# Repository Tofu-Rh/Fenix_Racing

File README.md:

<!--  -->

# <div align="center"> Repositório Eletrônica </div>

##### Por Rhomulo Thiago (com "h" nos dois)

<p align="justify">Este repositório é destinado ao armazenamento, consulta e utilização de informações relacionadas a programação de sistemas embarcados na área da Eletrônica. Cada pasta é separada pelo nome de um software específico utilizado, contendo guias para novos membros e suas aplicações para a equipe. Abaixo tem-se o link para cada uma das pastas : </p>

- [Arduino IDE](https://github.com/Tofu-Rh/Fenix_Racing/tree/main/Arduino%20IDE)
- [STM32Cube](https://github.com/Tofu-Rh/Fenix_Racing/tree/main/STM32)
- [VScode](https://github.com/Tofu-Rh/Fenix_Racing/tree/main/VScode)

### Tenho interesse em aprender a modificar os arquivos do repositório, como posso fazer isso?
<p align="justify"> O GitHub é uma plataforma de hospedagem de código-fonte e colaboração para desenvolvedores. Ele fornece um ambiente centralizado para gerenciar projetos de software usando o sistema de controle de versão Git. Este site, que você está acessando, contém apenas o repositório nosso hospedado, porém é possível criar e modificar este repositório remotamente do seu computador. Todo este controle entre repositório remoto (Seu computador) com o do Github (Esta página) é feito através do Git Dash, um software indispensável, que ensinarei sua utilização passo a passo abaixo:  </p>

## 1. Instalação do Git 
Caso esteja utilizando o sistema operacional Windows, é necessário instalar o Git no seu PC pelo link a seguir: [Download do Git para Windows](https://git-scm.com/download/win).

Para usuários de macOS e Linux, o Git pode ser instalado diretamente através do gerenciador de pacotes. Para macOS, você pode usar o Homebrew com o comando `brew install git`. No Linux, geralmente o comando é `sudo apt-get install git` (para distribuições baseadas no Debian/Ubuntu) ou `sudo yum install git` (para distribuições baseadas no Red Hat/Fedora).

## 2. Configuração Inicial
Após a instalação do Git, configure seu nome de usuário e e-mail para os commits:
```bash
git config --global user.name "Seu Nome"
git config --global user.email "seuemail@example.com"
```
## 3. Clonando o Repositório
Para começar a trabalhar com o repositório, clone-o para o seu computador:
```bash
git clone https://github.com/Tofu-Rh/Fenix_Racing.git
```
## 4. Fazendo Alterações
Navegue até o diretório do repositório clonado:
```bash
cd Fenix_Racing
```
Crie uma nova branch para suas alterações:
```bash
git checkout -b nome-da-sua-branch
```
Faça suas alterações e adicione os arquivos modificados. Em seguida você podera dar commit das mudanças(pre-etapa para envia-las, comente bem oq você está alterando):
```bash
git add .
git commit -m "Descrição das alterações realizadas"
```

## 5. Enviando Alterações para o Repositório Remoto
Para enviar suas alterações para o GitHub, use o comando:
```bash
git push origin nome-da-sua-branch
```

## 6. Atualizando seu Repositório Local
Para atualizar seu repositório local com as últimas alterações do repositório remoto:
```bash
git pull origin main
```
## Ademais Comandos
Outros comandos para utilizar pelo git não são os mais utilizados, porém podem servir de valor:
 Para ver as alterações que foram feitas desde o último commit:
```bash
git diff
```
Para visualizar o histórico de commits do repositório:
```bash
git log (Para visualizar o histórico de commits do repositório:
```

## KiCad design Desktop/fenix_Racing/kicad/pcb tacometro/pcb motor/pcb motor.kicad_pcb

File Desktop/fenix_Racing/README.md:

<!--  -->

# <div align="center"> Repositório Eletrônica </div>

##### Por Rhomulo Thiago (com "h" nos dois)

Todos os projetos deste repositório estão organizados em branch's separadas pelo nome do software em específico utilizado pela área. Atente-se a nomeclatura seguida em cada um deles, para não virar bagunça. 

Se tá perdido e começou agora com o git de uma olhada nessa playlist :  https://youtube.com/playlist?list=PL9jCCY-sD3m-fLgYBpKHWVlHaEz9MDBnw

Lista de comandos do git : https://docs.google.com/document/d/13YfJPmGhQXhTQrYP2JQ6DnHkJQH8FnN9acvRIVPWNEk/edit?usp=sharing

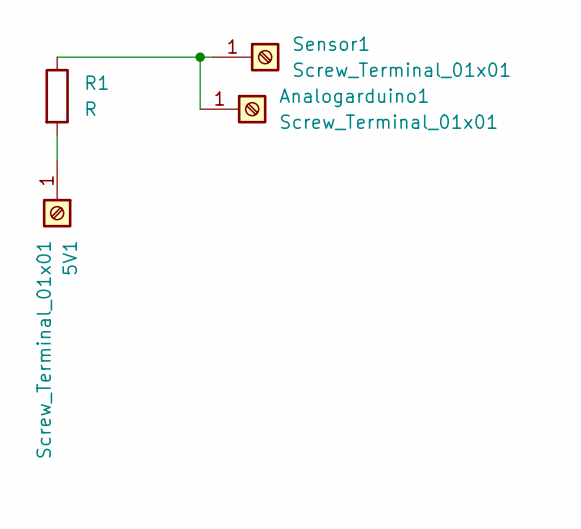
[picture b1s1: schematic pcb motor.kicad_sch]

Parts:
5V1: Screw_Terminal_01x01; TerminalBlock_MetzConnect_360271_1x01_Horizontal_ScrewM3.0_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
Analogarduino1: Screw_Terminal_01x01; TerminalBlock_MetzConnect_360271_1x01_Horizontal_ScrewM3.0_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
R1: R; R_Axial_DIN0411_L9.9mm_D3.6mm_P12.70mm_Horizontal
Sensor1: Screw_Terminal_01x01; TerminalBlock_MetzConnect_360271_1x01_Horizontal_ScrewM3.0_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

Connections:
unnamed: 5V1.1, R1.2
unnamed: Analogarduino1.1, R1.1, Sensor1.1

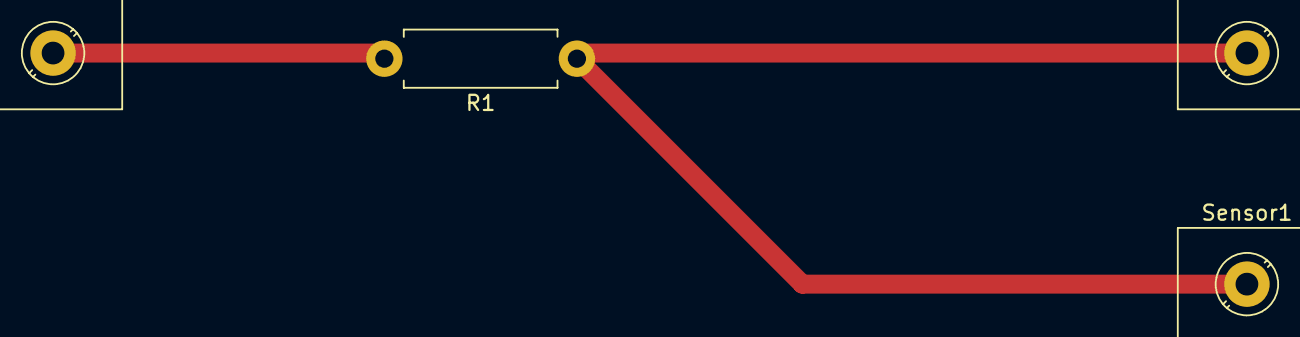
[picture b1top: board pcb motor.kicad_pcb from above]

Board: 2 copper layers, 4 parts (0 on the bottom side), 2 nets.

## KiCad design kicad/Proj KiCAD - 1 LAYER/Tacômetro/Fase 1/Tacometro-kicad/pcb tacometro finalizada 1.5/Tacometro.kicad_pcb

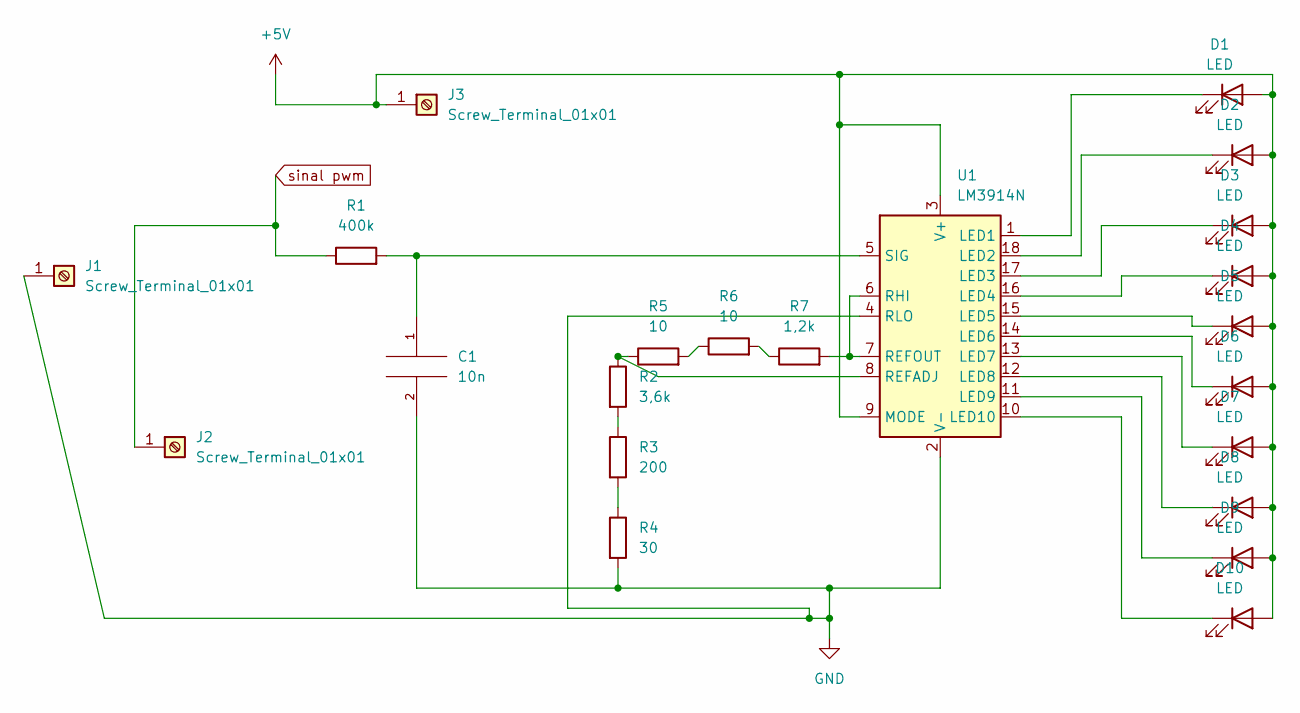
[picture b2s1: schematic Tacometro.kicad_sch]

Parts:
C1: 10n; C_Disc_D16.0mm_W5.0mm_P10.00mm
D1, D2, D3, D4, D5, D6, D7, D8, D9, D10: LED; LED_D5.0mm
J1, J2, J3: Screw_Terminal_01x01; PinHeader_1x01_P1.00mm_Vertical
R1: 400k; R_Axial_DIN0207_L6.3mm_D2.5mm_P10.16mm_Horizontal
R2: 3,6k; R_Axial_DIN0207_L6.3mm_D2.5mm_P10.16mm_Horizontal
R3: 200; R_Axial_DIN0207_L6.3mm_D2.5mm_P10.16mm_Horizontal
R4: 30; R_Axial_DIN0207_L6.3mm_D2.5mm_P10.16mm_Horizontal
R5, R6: 10; R_Axial_DIN0207_L6.3mm_D2.5mm_P10.16mm_Horizontal
R7: 1,2k; R_Axial_DIN0207_L6.3mm_D2.5mm_P10.16mm_Horizontal
U1: LM3914N; DIP-18_W7.62mm

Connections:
+5V: D1.2 (A), D2.2 (A), D3.2 (A), D4.2 (A), D5.2 (A), D6.2 (A), D7.2 (A), D8.2 (A), D9.2 (A), D10.2 (A), J3.1, U1.3 (V+), U1.9 (MODE)
GND: C1.2, J1.1, R4.2, U1.2 (V-), U1.4 (RLO)
unnamed: C1.1, R1.2, U1.5 (SIG)
unnamed: D1.1 (K), U1.1 (LED1)
unnamed: D2.1 (K), U1.18 (LED2)
unnamed: D3.1 (K), U1.17 (LED3)
unnamed: D4.1 (K), U1.16 (LED4)
unnamed: D5.1 (K), U1.15 (LED5)
unnamed: D6.1 (K), U1.14 (LED6)
unnamed: D7.1 (K), U1.13 (LED7)
unnamed: D8.1 (K), U1.12 (LED8)
unnamed: D9.1 (K), U1.11 (LED9)
unnamed: D10.1 (K), U1.10 (LED10)
unnamed: R2.1, R5.1, U1.8 (REFADJ)
unnamed: R2.2, R3.1
unnamed: R3.2, R4.1
unnamed: R5.2, R6.1
unnamed: R6.2, R7.1
unnamed: R7.2, U1.6 (RHI), U1.7 (REFOUT)
sinal pwm: J2.1, R1.1

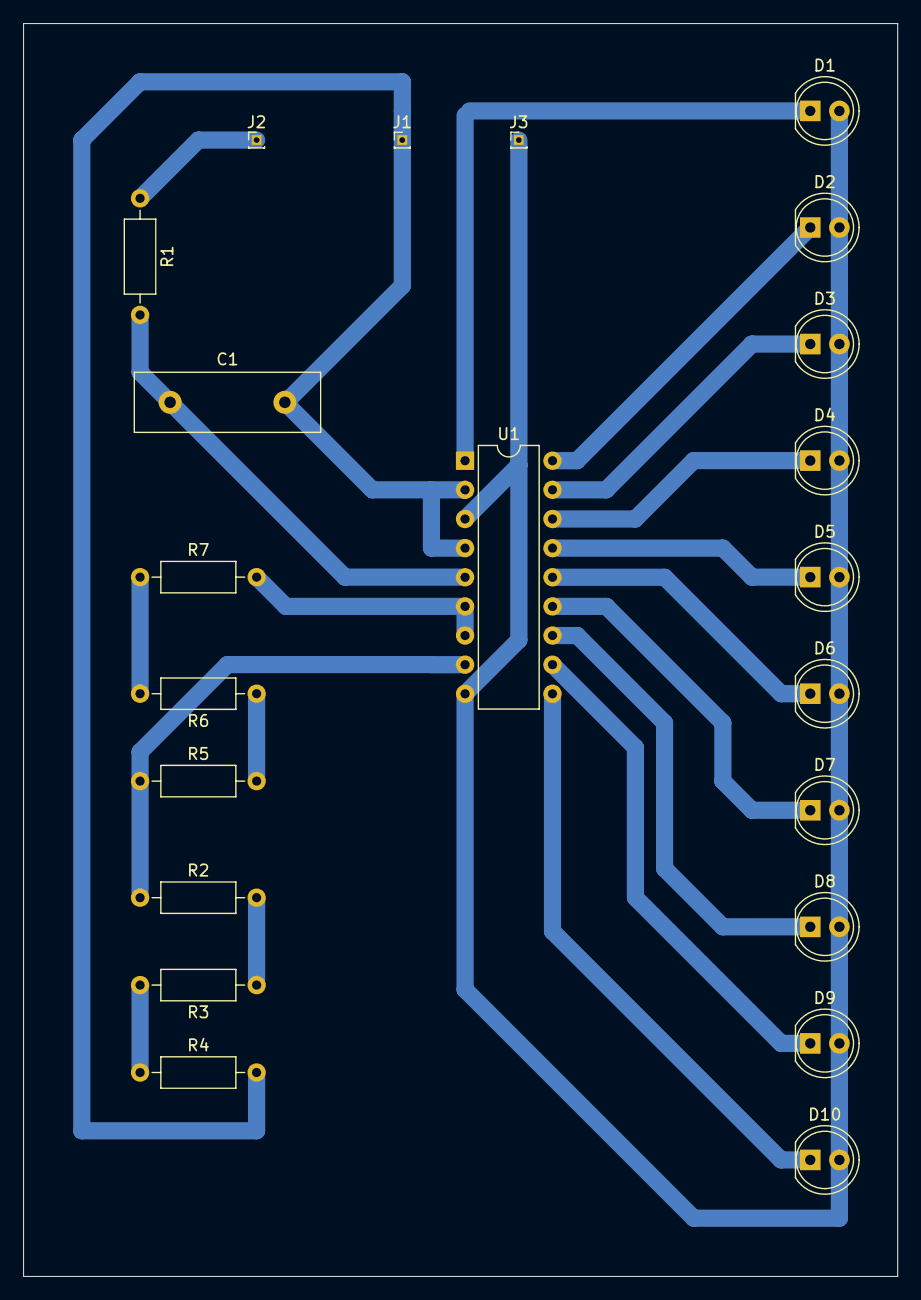
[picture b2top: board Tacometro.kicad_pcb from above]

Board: 2 copper layers, 76.2 x 109.2 mm, 22 parts (0 on the bottom side), 20 nets.

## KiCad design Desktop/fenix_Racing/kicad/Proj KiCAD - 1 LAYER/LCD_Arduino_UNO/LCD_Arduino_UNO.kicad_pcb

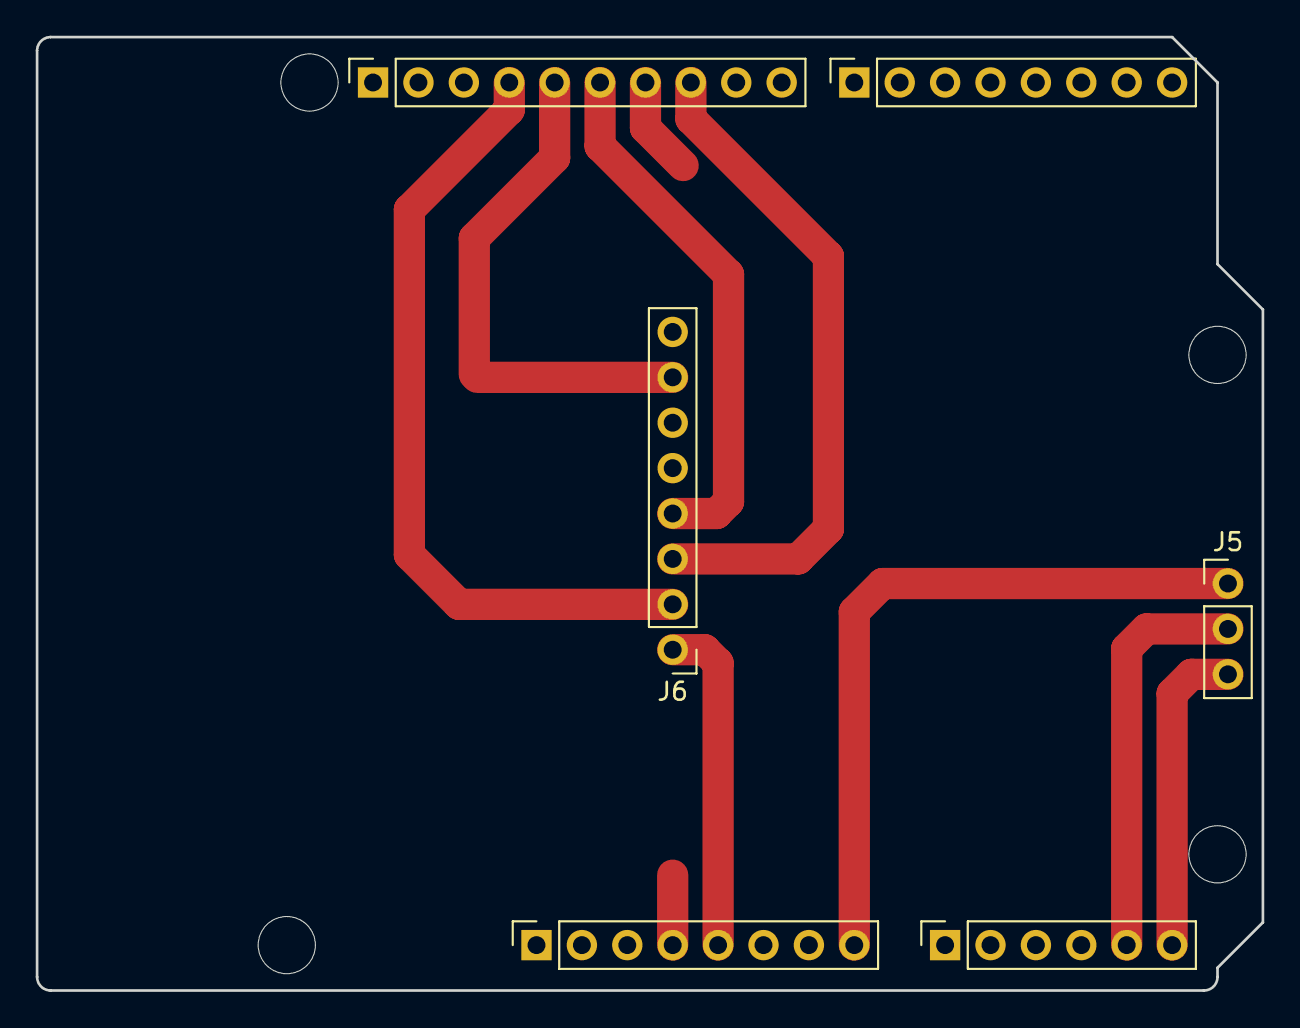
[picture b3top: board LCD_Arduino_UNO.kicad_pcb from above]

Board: 2 copper layers, 68.6 x 53.3 mm, 10 parts (0 on the bottom side), 9 nets.

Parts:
J1: Power; PinSocket_1x08_P2.54mm_Vertical
J2: Digital/PWM; PinSocket_1x10_P2.54mm_Vertical
J3: Analog; PinSocket_1x06_P2.54mm_Vertical
J4: Digital/PWM; PinSocket_1x08_P2.54mm_Vertical
J5: pinos; PinHeader_1x03_P2.54mm_Vertical
J6: LCD; PinHeader_1x08_P2.54mm_Vertical
MH1, MH2, MH3, MH4: MountingHole_3.2mm

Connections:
+5V: J1.5, J6.1
/12: J2.6, J6.4
/13: J2.5, J6.7
/*10: J2.8, J6.3
/*11: J2.7, J6.6
/SCL/A5: J2.1, J3.6, J5.3
/SDA/A4: J2.2, J3.5, J5.2
GND: J1.6, J1.7, J2.4, J6.2
VCC: J1.8, J5.1

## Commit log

2023-05-02 Arquivos
2023-05-03 primeira versao com index html
2023-05-03 Main
2023-05-03 kicad
2023-05-03 Mudança no Readme
2023-05-03 Arduino pasta
2023-05-03 Arduino
2023-05-04 Kicad projetos
2023-05-04 Modificações cod
2023-05-16 “mensagem”
2023-05-23 pcb do tacometro
2024-01-02 01/01/24
2024-01-02 Arduino texto
2024-01-02 ibagem
2024-01-02 2/1/24
2024-01-02 2/12/202
2024-01-02 2/12/2024
2024-08-22 Att Free_RTOS LIB
2024-10-17 Queue test
2024-10-18 Att corna
2024-12-01 Create LICENSE
